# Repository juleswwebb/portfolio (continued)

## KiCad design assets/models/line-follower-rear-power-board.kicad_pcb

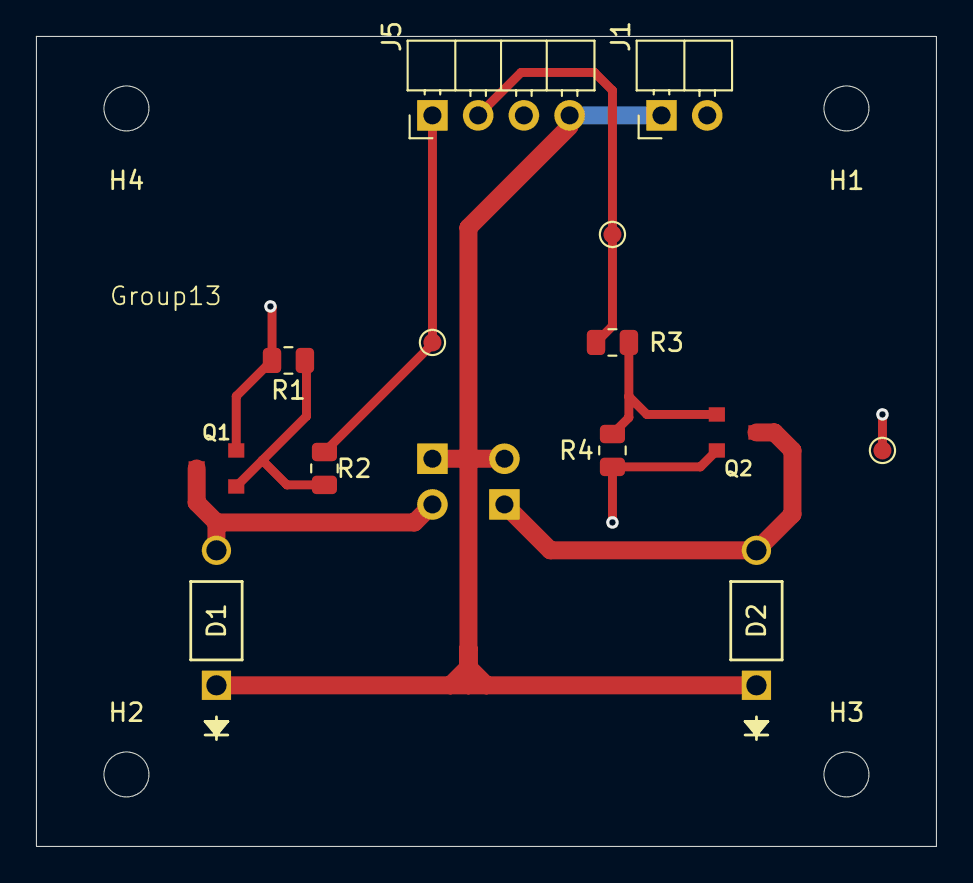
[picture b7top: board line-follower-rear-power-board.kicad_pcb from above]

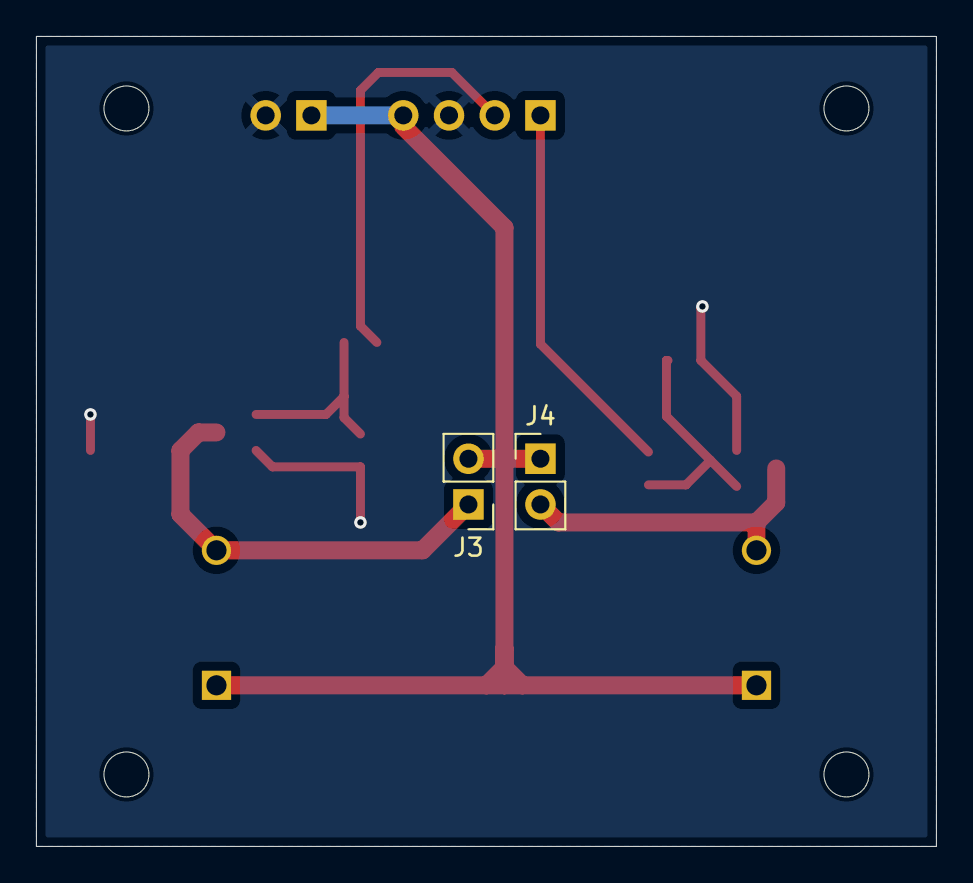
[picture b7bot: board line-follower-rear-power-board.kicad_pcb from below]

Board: 2 copper layers, 50.0 x 45.0 mm, 19 parts (2 on the bottom side), 8 nets.

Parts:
D1, D2: D; DO-41_DIO
H1, H2, H3, H4: MountingHole; MountingHole_2.5mm
J1: Battery; PinHeader_1x02_P2.54mm_Horizontal
J3: Motor2; PinHeader_1x02_P2.54mm_Vertical
J4: Motor1; PinHeader_1x02_P2.54mm_Vertical
J5: Conn_01x04; PinHeader_1x04_P2.54mm_Horizontal
Q1, Q2: NMOS; TRANS_BC846B_215
R1, R4: 10k; R_0805_2012Metric
R2, R3: 220; R_0805_2012Metric
TP1, TP2, TP3: TestPoint; TestPoint_Pad_D1.0mm

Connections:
GND: J1.2, J5.3, Q1.2 (S), Q2.2 (S), R1.2, R4.2, TP3.1
unnamed: D1.2 (A), J4.2, Q1.3 (D)
unnamed: D2.2 (A), J3.1, Q2.3 (D)
unnamed: J5.1, R2.1, TP2.1
unnamed: J5.2, R3.1, TP1.1
unnamed: Q1.1 (G), R1.1, R2.2
unnamed: Q2.1 (G), R3.2, R4.1
Vdd: D1.1 (K), D2.1 (K), J1.1, J3.2, J4.1, J5.4

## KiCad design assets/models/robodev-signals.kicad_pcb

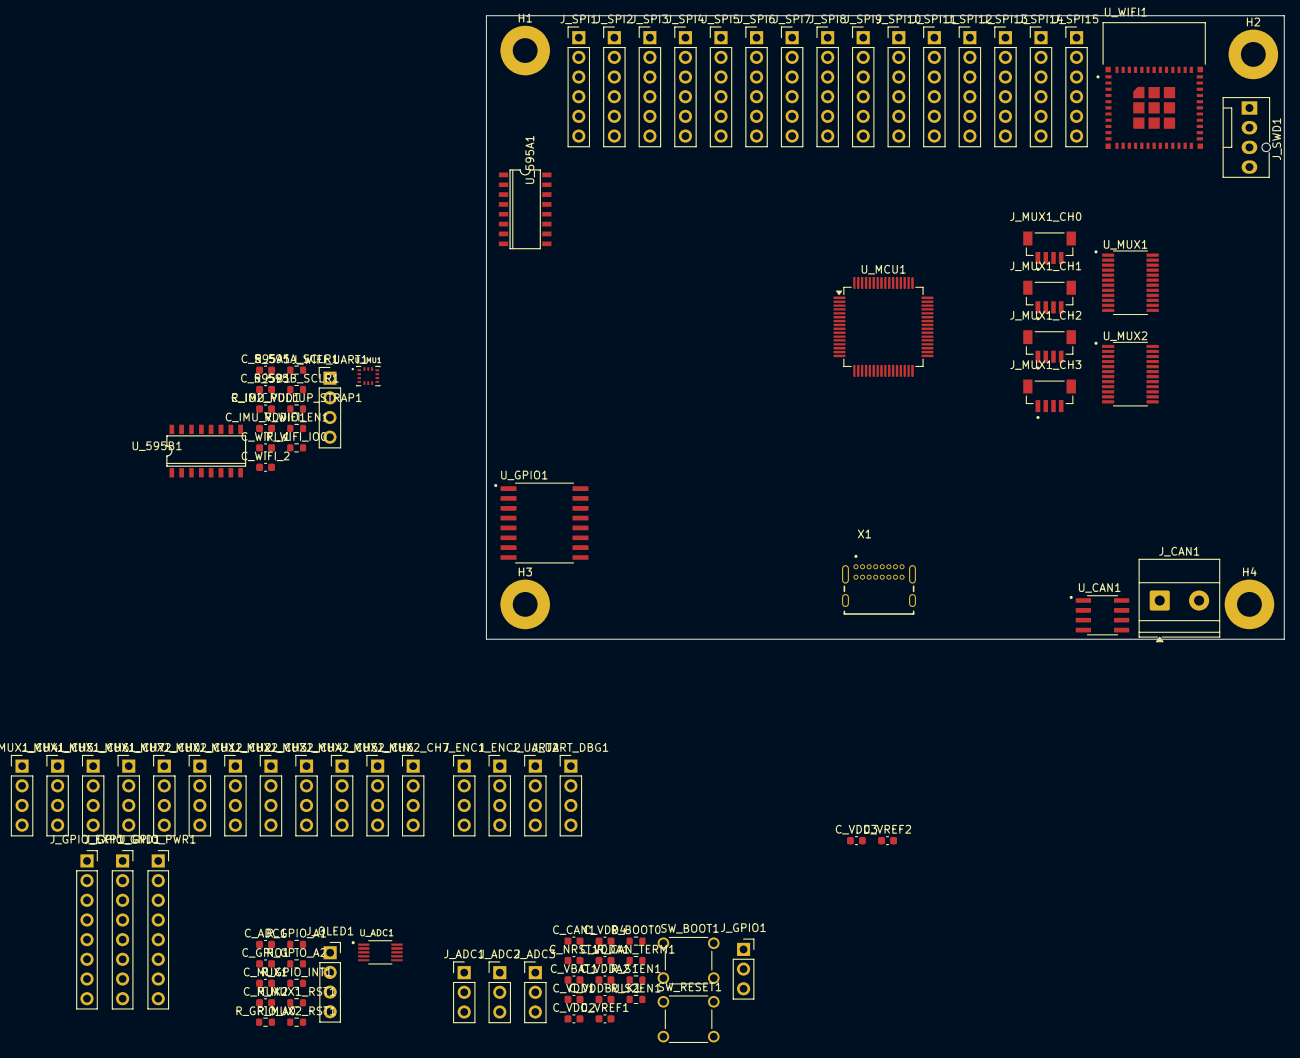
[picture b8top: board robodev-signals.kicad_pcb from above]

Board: 4 copper layers, 103.0 x 80.5 mm, 100 parts (0 on the bottom side), 103 nets, no tracks yet.

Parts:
C_595A1, C_595B1: 100 nF 10V X7R; C_0603_1608Metric
C_ADC1: 100 nF 10V X7R; C_0603_1608Metric
C_CAN1: 100 nF 10V X7R; C_0603_1608Metric
C_GPIO1: 100 nF 10V X7R; C_0603_1608Metric
C_IMU_VDD1: 100 nF 10V X7R; C_0603_1608Metric
C_IMU_VDDIO1: 100 nF 10V X7R; C_0603_1608Metric
C_MUX1, C_MUX2: 100 nF 10V X7R; C_0603_1608Metric
C_NRST1: 100 nF 10V X7R; C_0603_1608Metric
C_VBAT1: 100 nF 10V X7R; C_0603_1608Metric
C_VDD1, C_VDD2, C_VDD3, C_VDD4: 100 nF 10V X7R; C_0603_1608Metric
C_VDDA1: 1 µF 10V X5R; C_0603_1608Metric
C_VDDA2: 10 nF 10V X7R; C_0603_1608Metric
C_VDDBULK1: 4.7 µF 10V X5R; C_0603_1608Metric
C_VREF1: 1 µF 10V X5R; C_0603_1608Metric
C_VREF2: 100 nF 10V X7R; C_0603_1608Metric
C_WIFI_1: 10 µF 10V X5R; C_0603_1608Metric
C_WIFI_2: 100 nF 10V X7R; C_0603_1608Metric
H1, H2, H3, H4: MountingHole_Pad; MountingHole_3.2mm_M3_Pad
J_ADC1, J_ADC2, J_ADC3: ADC Header 2.54mm; PinHeader_1x03_P2.54mm_Vertical
J_CAN1: CAN Bus 5.08mm; TerminalBlock_Phoenix_MKDS-1,5-2-5.08_1x02_P5.08mm_Horizont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
J_ENC1: Encoder 1 2.54mm; PinHeader_1x04_P2.54mm_Vertical
J_ENC2: Encoder 2 2.54mm; PinHeader_1x04_P2.54mm_Vertical
J_GPIO1: GPIO Header 2.54mm; PinSocket_1x03_P2.54mm_Vertical
J_GPIO_EXP1: Conn_01x08_F; PinSocket_1x08_P2.54mm_Vertical
J_GPIO_GND1: Conn_01x08F; PinSocket_1x08_P2.54mm_Vertical
J_GPIO_PWR1: Conn_01x08F; PinSocket_1x08_P2.54mm_Vertical
J_MUX1_CH0, J_MUX1_CH1, J_MUX1_CH2, J_MUX1_CH3: QWIIC I2C 2.54mm Header; ADAFRUIT_4328
J_MUX1_CH4, J_MUX1_CH5, J_MUX1_CH6, J_MUX1_CH7, J_MUX2_CH0, J_MUX2_CH1, J_MUX2_CH2, J_MUX2_CH3, J_MUX2_CH4, J_MUX2_CH5, J_MUX2_CH6, J_MUX2_CH7: I2C 2.54mm Header; PinHeader_1x04_P2.54mm_Vertical
J_OLED1: Conn_01x04; PinSocket_1x04_P2.54mm_Vertical
J_SPI1, J_SPI2, J_SPI3, J_SPI4, J_SPI5, J_SPI6, J_SPI7, J_SPI8, J_SPI9, J_SPI10, J_SPI11, J_SPI12, J_SPI13, J_SPI14, J_SPI15: SPI Expansion 2.54mm; PinHeader_1x06_P2.54mm_Vertical
J_SWD1: SWD Debug 2.54mm; FanPinHeader_1x04_P2.54mm_Vertical
J_UART2: UART General 2.54mm; PinHeader_1x04_P2.54mm_Vertical
J_UART_DBG1: UART Debug 2.54mm; PinHeader_1x04_P2.54mm_Vertical
J_WIFI_UART1: WiFi UART 2.54mm; PinHeader_1x04_P2.54mm_Vertical
R_595A_SCLR1, R_595B_SCLR1: 10 kΩ 1% 0603; R_0603_1608Metric
R_BOOT0: 10 kΩ 1% 0603; R_0603_1608Metric
R_CAN_TERM1: 120 Ω 1% 0603; R_0603_1608Metric
R_GPIO_A0, R_GPIO_A1, R_GPIO_A2: 100 kΩ 1% 0603; R_0603_1608Metric
R_GPIO_INT1: 10 kΩ 1% 0603; R_0603_1608Metric
R_IO2_PULLUP_STRAP1: 10 kΩ 1% 0603; R_0603_1608Metric
R_MUX1_RST1, R_MUX2_RST1: 10 kΩ 1% 0603; R_0603_1608Metric
R_S1EN1, R_S2EN1: 10 kΩ 1% 0603; R_0603_1608Metric
R_WIFI_EN1: 10 kΩ 1% 0603; R_0603_1608Metric
R_WIFI_IO0: 10 kΩ 1% 0603; R_0603_1608Metric
SW_BOOT1: MJTP1230; SW_MJTP1230
SW_RESET1: MJTP1230; SW_MJTP1230
U_595A1, U_595B1: 74HC595; SO16
U_ADC1: ADS1115IDGST; SOP50P490X110-10N
U_CAN1: SN65HVD230D; SOIC127P599X175-8N
U_GPIO1: PCF8574DW; SOIC127P1030X265-16N
U_IMU1: BMI270; XDCR_BMI270
U_MCU1: STM32G431RBTx; LQFP-64_10x10mm_P0.5mm
U_MUX1, U_MUX2: TCA9548APWR; SOP65P640X120-24N
U_WIFI1: ESP32-C3-MINI-1-N4; XCVR_ESP32-C3-MINI-1-N4
X1: USB4085-GF-A; GCT_USB4085-GF-A_REVB

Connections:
+3V3: C_595A1.2, C_595B1.2, C_ADC1.2, C_CAN1.2, C_GPIO1.2, C_IMU_VDD1.1, C_IMU_VDDIO1.2, C_MUX1.2, C_MUX2.2, C_VBAT1.2, C_VDD1.1, C_VDD2.1, C_VDD3.2, C_VDD4.1, C_VDDA1.2, C_VDDA2.2, C_VDDBULK1.2, C_VREF1.2, C_VREF2.2, C_WIFI_1.2, C_WIFI_2.2, J_ADC1.2, J_ADC2.2, J_ADC3.2, J_ENC1.2, J_ENC2.2, J_GPIO1.2, J_GPIO_PWR1.1, J_GPIO_PWR1.2, J_GPIO_PWR1.3, J_GPIO_PWR1.4, J_GPIO_PWR1.5, J_GPIO_PWR1.6, J_GPIO_PWR1.7, J_GPIO_PWR1.8, J_MUX1_CH0.2, J_MUX1_CH1.2, J_MUX1_CH2.2, J_MUX1_CH3.2, J_MUX1_CH4.2, J_MUX1_CH5.2, J_MUX1_CH6.2, J_MUX1_CH7.2, J_MUX2_CH0.2, J_MUX2_CH1.2, J_MUX2_CH2.2, J_MUX2_CH3.2, J_MUX2_CH4.2, J_MUX2_CH5.2, J_MUX2_CH6.2, J_MUX2_CH7.2, J_OLED1.1, J_SPI1.2, J_SPI2.2, J_SPI3.2, J_SPI4.2, J_SPI5.2, J_SPI6.2, J_SPI7.2, J_SPI8.2, J_SPI9.2, J_SPI10.2, J_SPI11.2, J_SPI12.2, J_SPI13.2, J_SPI14.2, J_SPI15.2, J_SWD1.1, J_UART2.2, J_UART_DBG1.2, J_WIFI_UART1.2, R_595A_SCLR1.1, R_595B_SCLR1.1, R_GPIO_INT1.1, R_IO2_PULLUP_STRAP1.1, R_MUX1_RST1.1, R_MUX2_RST1.1, R_S1EN1.1, R_S2EN1.1, R_WIFI_EN1.1, R_WIFI_IO0.1, SW_BOOT1.2_1, U_595A1.16 (VCC), U_595B1.16 (VCC), U_ADC1.8 (VDD), U_CAN1.3 (VCC), U_GPIO1.16 (VCC), U_IMU1.5 (VDDIO), U_IMU1.8 (VDD), U_MCU1.1 (VBAT), U_MCU1.16 (VDD), U_MCU1.28 (VREF+), U_MCU1.29 (VDDA), U_MCU1.32 (VDD), U_MCU1.48 (VDD), U_MCU1.64 (VDD), U_MUX1.24 (VCC), U_MUX2.1 (A0), U_MUX2.24 (VCC), U_WIFI1.3 (3V3)
/i2c_bus/GPIO_INT: R_GPIO_INT1.2, U_GPIO1.13 (~INT)
/i2c_bus/GPIO_P0: J_GPIO_EXP1.1, U_GPIO1.4 (P0)
/i2c_bus/GPIO_P1: J_GPIO_EXP1.2, U_GPIO1.5 (P1)
/i2c_bus/GPIO_P2: J_GPIO_EXP1.3, U_GPIO1.6 (P2)
/i2c_bus/GPIO_P3: J_GPIO_EXP1.4, U_GPIO1.7 (P3)
/i2c_bus/GPIO_P4: J_GPIO_EXP1.5, U_GPIO1.9 (P4)
/i2c_bus/GPIO_P5: J_GPIO_EXP1.6, U_GPIO1.10 (P5)
/i2c_bus/GPIO_P6: J_GPIO_EXP1.7, U_GPIO1.11 (P6)
/i2c_bus/GPIO_P7: J_GPIO_EXP1.8, U_GPIO1.12 (P7)
/i2c_bus/I2C_SCL: J_OLED1.3, U_ADC1.10 (SCL), U_GPIO1.14 (SCL), U_MUX1.22 (SCL), U_MUX2.22 (SCL)
/i2c_bus/I2C_SDA: J_OLED1.4, U_ADC1.9 (SDA), U_GPIO1.15 (SDA), U_MUX1.23 (SDA), U_MUX2.23 (SDA)
/i2c_bus/MUX1_SC0: J_MUX1_CH0.4, U_MUX1.5 (SC0)
/i2c_bus/MUX1_SC1: J_MUX1_CH1.4, U_MUX1.7 (SC1)
/i2c_bus/MUX1_SC2: J_MUX1_CH2.4, U_MUX1.9 (SC2)
/i2c_bus/MUX1_SC3: J_MUX1_CH3.4, U_MUX1.11 (SC3)
/i2c_bus/MUX1_SC4: J_MUX1_CH4.4, U_MUX1.14 (SC4)
/i2c_bus/MUX1_SC5: J_MUX1_CH5.4, U_MUX1.16 (SC5)
/i2c_bus/MUX1_SC6: J_MUX1_CH6.4, U_MUX1.18 (SC6)
/i2c_bus/MUX1_SC7: J_MUX1_CH7.4, U_MUX1.20 (SC7)
/i2c_bus/MUX1_SD0: J_MUX1_CH0.3, U_MUX1.4 (SD0)
/i2c_bus/MUX1_SD1: J_MUX1_CH1.3, U_MUX1.6 (SD1)
/i2c_bus/MUX1_SD2: J_MUX1_CH2.3, U_MUX1.8 (SD2)
/i2c_bus/MUX1_SD3: J_MUX1_CH3.3, U_MUX1.10 (SD3)
/i2c_bus/MUX1_SD4: J_MUX1_CH4.3, U_MUX1.13 (SD4)
/i2c_bus/MUX1_SD5: J_MUX1_CH5.3, U_MUX1.15 (SD5)
/i2c_bus/MUX1_SD6: J_MUX1_CH6.3, U_MUX1.17 (SD6)
/i2c_bus/MUX1_SD7: J_MUX1_CH7.3, U_MUX1.19 (SD7)
/i2c_bus/MUX2_SC0: J_MUX2_CH0.4, U_MUX2.5 (SC0)
/i2c_bus/MUX2_SC1: J_MUX2_CH1.4, U_MUX2.7 (SC1)
/i2c_bus/MUX2_SC2: J_MUX2_CH2.4, U_MUX2.9 (SC2)
/i2c_bus/MUX2_SC3: J_MUX2_CH3.4, U_MUX2.11 (SC3)
/i2c_bus/MUX2_SC4: J_MUX2_CH4.4, U_MUX2.14 (SC4)
/i2c_bus/MUX2_SC5: J_MUX2_CH5.4, U_MUX2.16 (SC5)
/i2c_bus/MUX2_SC6: J_MUX2_CH6.4, U_MUX2.18 (SC6)
/i2c_bus/MUX2_SC7: J_MUX2_CH7.4, U_MUX2.20 (SC7)
/i2c_bus/MUX2_SD0: J_MUX2_CH0.3, U_MUX2.4 (SD0)
/i2c_bus/MUX2_SD1: J_MUX2_CH1.3, U_MUX2.6 (SD1)
/i2c_bus/MUX2_SD2: J_MUX2_CH2.3, U_MUX2.8 (SD2)
/i2c_bus/MUX2_SD3: J_MUX2_CH3.3, U_MUX2.10 (SD3)
/i2c_bus/MUX2_SD4: J_MUX2_CH4.3, U_MUX2.13 (SD4)
/i2c_bus/MUX2_SD5: J_MUX2_CH5.3, U_MUX2.15 (SD5)
/i2c_bus/MUX2_SD6: J_MUX2_CH6.3, U_MUX2.17 (SD6)
/i2c_bus/MUX2_SD7: J_MUX2_CH7.3, U_MUX2.19 (SD7)
/spi_bus/SPI_CS0: U_595A1.15 (QA), U_IMU1.12 (CSB)
/spi_bus/SPI_CS1: J_SPI1.3, U_595A1.1 (QB)
/spi_bus/SPI_CS2: J_SPI2.3, U_595A1.2 (QC)
/spi_bus/SPI_CS3: J_SPI3.3, U_595A1.3 (QD)
/spi_bus/SPI_CS4: J_SPI4.3, U_595A1.4 (QE)
/spi_bus/SPI_CS5: J_SPI5.3, U_595A1.5 (QF)
/spi_bus/SPI_CS6: J_SPI6.3, U_595A1.6 (QG)
/spi_bus/SPI_CS7: J_SPI7.3, U_595A1.7 (QH)
/spi_bus/SPI_CS8: J_SPI8.3, U_595B1.15 (QA)
/spi_bus/SPI_CS9: J_SPI9.3, U_595B1.1 (QB)
/spi_bus/SPI_CS10: J_SPI10.3, U_595B1.2 (QC)
/spi_bus/SPI_CS11: J_SPI11.3, U_595B1.3 (QD)
/spi_bus/SPI_CS12: J_SPI12.3, U_595B1.4 (QE)
/spi_bus/SPI_CS13: J_SPI13.3, U_595B1.5 (QF)
/spi_bus/SPI_CS14: J_SPI14.3, U_595B1.6 (QG)
/spi_bus/SPI_CS15: J_SPI15.3, U_595B1.7 (QH)
/spi_bus/SPI_LATCH: U_595A1.12 (RCLK), U_595B1.12 (RCLK)
/spi_bus/SPI_MISO: J_SPI1.6, J_SPI2.6, J_SPI3.6, J_SPI4.6, J_SPI5.6, J_SPI6.6, J_SPI7.6, J_SPI8.6, J_SPI9.6, J_SPI10.6, J_SPI11.6, J_SPI12.6, J_SPI13.6, J_SPI14.6, J_SPI15.6, R_IO2_PULLUP_STRAP1.2, U_IMU1.1 (SDO), U_WIFI1.5 (IO2)
/spi_bus/SPI_MOSI: J_SPI1.5, J_SPI2.5, J_SPI3.5, J_SPI4.5, J_SPI5.5, J_SPI6.5, J_SPI7.5, J_SPI8.5, J_SPI9.5, J_SPI10.5, J_SPI11.5, J_SPI12.5, J_SPI13.5, J_SPI14.5, J_SPI15.5, U_595A1.14 (SER), U_IMU1.14 (SDX), U_WIFI1.21 (IO7)
/spi_bus/SPI_SCK: J_SPI1.4, J_SPI2.4, J_SPI3.4, J_SPI4.4, J_SPI5.4, J_SPI6.4, J_SPI7.4, J_SPI8.4, J_SPI9.4, J_SPI10.4, J_SPI11.4, J_SPI12.4, J_SPI13.4, J_SPI14.4, J_SPI15.4, U_595A1.11 (SCLK), U_595B1.11 (SCLK), U_IMU1.13 (SCX), U_WIFI1.20 (IO6)
/spi_bus/WIFI_RXD: J_WIFI_UART1.3, U_WIFI1.30 (RXD0)
/spi_bus/WIFI_TXD: J_WIFI_UART1.4, U_WIFI1.31 (TXD0)
/stm32/ADC_A1: J_ADC1.3, U_MCU1.34 (PB12)
/stm32/ADC_A2: J_ADC2.3, U_MCU1.36 (PB14)
/stm32/ADC_A3: J_ADC3.3, U_MCU1.37 (PB15)
/stm32/CAN_RX: R_BOOT0.1, SW_BOOT1.1_1, U_CAN1.4 (R), U_MCU1.61 (PB8)
/stm32/CAN_TX: U_CAN1.1 (D), U_MCU1.62 (PB9)
/stm32/ENC1_A: J_ENC1.3, U_MCU1.12 (PA0)
/stm32/ENC1_B: J_ENC1.4, U_MCU1.13 (PA1)
/stm32/ENC2_A: J_ENC2.3, U_MCU1.38 (PC6)
/stm32/ENC2_B: J_ENC2.4, U_MCU1.39 (PC7)
/stm32/GPIO_PC13: J_GPIO1.3, U_MCU1.2 (PC13)
/stm32/NRST: C_NRST1.2, SW_RESET1.1_2, U_MCU1.7 (PG10)
/stm32/S1_EN: R_S1EN1.2, U_MCU1.26 (PB2)
/stm32/S2_EN: R_S2EN1.2, U_MCU1.55 (PD2)
/stm32/SWCLK: J_SWD1.3, U_MCU1.50 (PA14)
/stm32/SWDIO: J_SWD1.2, U_MCU1.49 (PA13)
/stm32/UART2_RX: J_UART2.4, U_MCU1.33 (PB11)
/stm32/UART2_TX: J_UART2.3, U_MCU1.30 (PB10)
/stm32/UART_DBG_RX: J_UART_DBG1.4, U_MCU1.44 (PA10)
/stm32/UART_DBG_TX: J_UART_DBG1.3, U_MCU1.43 (PA9)
/stm32/UCPD_CC1: U_MCU1.59 (PB6), X1.A5 (CC1)
/stm32/UCPD_CC2: U_MCU1.57 (PB4), X1.B5 (CC2)
/stm32/USB_DM: U_MCU1.45 (PA11), X1.A7 (DN1), X1.B7 (DN2)
/stm32/USB_DP: U_MCU1.46 (PA12), X1.A6 (DP1), X1.B6 (DP2)
GND: C_595A1.1, C_595B1.1, C_ADC1.1, C_CAN1.1, C_GPIO1.1, C_IMU_VDD1.2, C_IMU_VDDIO1.1, C_MUX1.1, C_MUX2.1, C_NRST1.1, C_VBAT1.1, C_VDD1.2, C_VDD2.2, C_VDD3.1, C_VDD4.2, C_VDDA1.1, C_VDDA2.1, C_VDDBULK1.1, C_VREF1.1, C_VREF2.1, C_WIFI_1.1, C_WIFI_2.1, H1.1, H2.1, H3.1, H4.1, J_ADC1.1, J_ADC2.1, J_ADC3.1, J_ENC1.1, J_ENC2.1, J_GPIO1.1, J_GPIO_GND1.1, J_GPIO_GND1.2, J_GPIO_GND1.3, J_GPIO_GND1.4, J_GPIO_GND1.5, J_GPIO_GND1.6, J_GPIO_GND1.7, J_GPIO_GND1.8, J_MUX1_CH0.1, J_MUX1_CH1.1, J_MUX1_CH2.1, J_MUX1_CH3.1, J_MUX1_CH4.1, J_MUX1_CH5.1, J_MUX1_CH6.1, J_MUX1_CH7.1, J_MUX2_CH0.1, J_MUX2_CH1.1, J_MUX2_CH2.1, J_MUX2_CH3.1, J_MUX2_CH4.1, J_MUX2_CH5.1, J_MUX2_CH6.1, J_MUX2_CH7.1, J_OLED1.2, J_SPI1.1, J_SPI2.1, J_SPI3.1, J_SPI4.1, J_SPI5.1, J_SPI6.1, J_SPI7.1, J_SPI8.1, J_SPI9.1, J_SPI10.1, J_SPI11.1, J_SPI12.1, J_SPI13.1, J_SPI14.1, J_SPI15.1, J_SWD1.4, J_UART2.1, J_UART_DBG1.1, J_WIFI_UART1.1, R_BOOT0.2, R_GPIO_A0.1, R_GPIO_A1.1, R_GPIO_A2.1, SW_RESET1.2_2, U_595A1.8 (GND), U_595A1.13 (~OE), U_595B1.8 (GND), U_595B1.13 (~OE), U_ADC1.1 (ADDR), U_ADC1.3 (GND), U_CAN1.2 (GND), U_CAN1.8 (RS), U_GPIO1.8 (GND), U_IMU1.6 (GNDIO), U_IMU1.7 (GND), U_MCU1.15 (VSS), U_MCU1.27 (VSSA), U_MCU1.31 (VSS), U_MCU1.47 (VSS), U_MCU1.63 (VSS), U_MUX1.1 (A0), U_MUX1.2 (A1), U_MUX1.12 (GND), U_MUX1.21 (A2), U_MUX2.2 (A1), U_MUX2.12 (GND), U_MUX2.21 (A2), U_WIFI1.1 (GND), U_WIFI1.2 (GND), U_WIFI1.11 (GND), U_WIFI1.14 (GND), U_WIFI1.36 (GND), U_WIFI1.37 (GND), U_WIFI1.38 (GND), U_WIFI1.39 (GND), U_WIFI1.40 (GND), U_WIFI1.41 (GND), U_WIFI1.42 (GND), U_WIFI1.43 (GND), U_WIFI1.44 (GND), U_WIFI1.45 (GND), U_WIFI1.46 (GND), U_WIFI1.47 (GND), U_WIFI1.48 (GND), U_WIFI1.49_1 (GND), U_WIFI1.49_2 (GND), U_WIFI1.49_3 (GND), U_WIFI1.49_4 (GND), U_WIFI1.49_5 (GND), U_WIFI1.49_6 (GND), U_WIFI1.49_7 (GND), U_WIFI1.49_8 (GND), U_WIFI1.49_9 (GND), U_WIFI1.50 (GND), U_WIFI1.51 (GND), U_WIFI1.52 (GND), U_WIFI1.53 (GND), X1.A1 (GND), X1.A12 (GND), X1.B1 (GND), X1.B12 (GND), X1.S1 (SHELL), X1.S2 (SHELL), X1.S3 (SHELL), X1.S4 (SHELL)
unnamed: J_CAN1.1, R_CAN_TERM1.1, U_CAN1.7 (CANH)
unnamed: J_CAN1.2, R_CAN_TERM1.2, U_CAN1.6 (CANL)
unnamed: U_595A1.9 (QH'), U_595B1.14 (SER)
unnamed: R_595A_SCLR1.2, U_595A1.10 (~SCLR)
unnamed: R_595B_SCLR1.2, U_595B1.10 (~SCLR)
unnamed: R_GPIO_A0.2, U_GPIO1.1 (A0)
unnamed: R_GPIO_A1.2, U_GPIO1.2 (A1)
unnamed: R_GPIO_A2.2, U_GPIO1.3 (A2)
unnamed: R_MUX1_RST1.2, U_MUX1.3 (~RESET)
unnamed: R_MUX2_RST1.2, U_MUX2.3 (~RESET)
unnamed: R_WIFI_EN1.2, U_WIFI1.8 (EN)
unnamed: R_WIFI_IO0.2, U_WIFI1.12 (IO0)
VBUS: X1.A4 (VBUS), X1.A9 (VBUS), X1.B4 (VBUS), X1.B9 (VBUS)
